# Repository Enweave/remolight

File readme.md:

### ... well, we just mess around with VUE and Wemos

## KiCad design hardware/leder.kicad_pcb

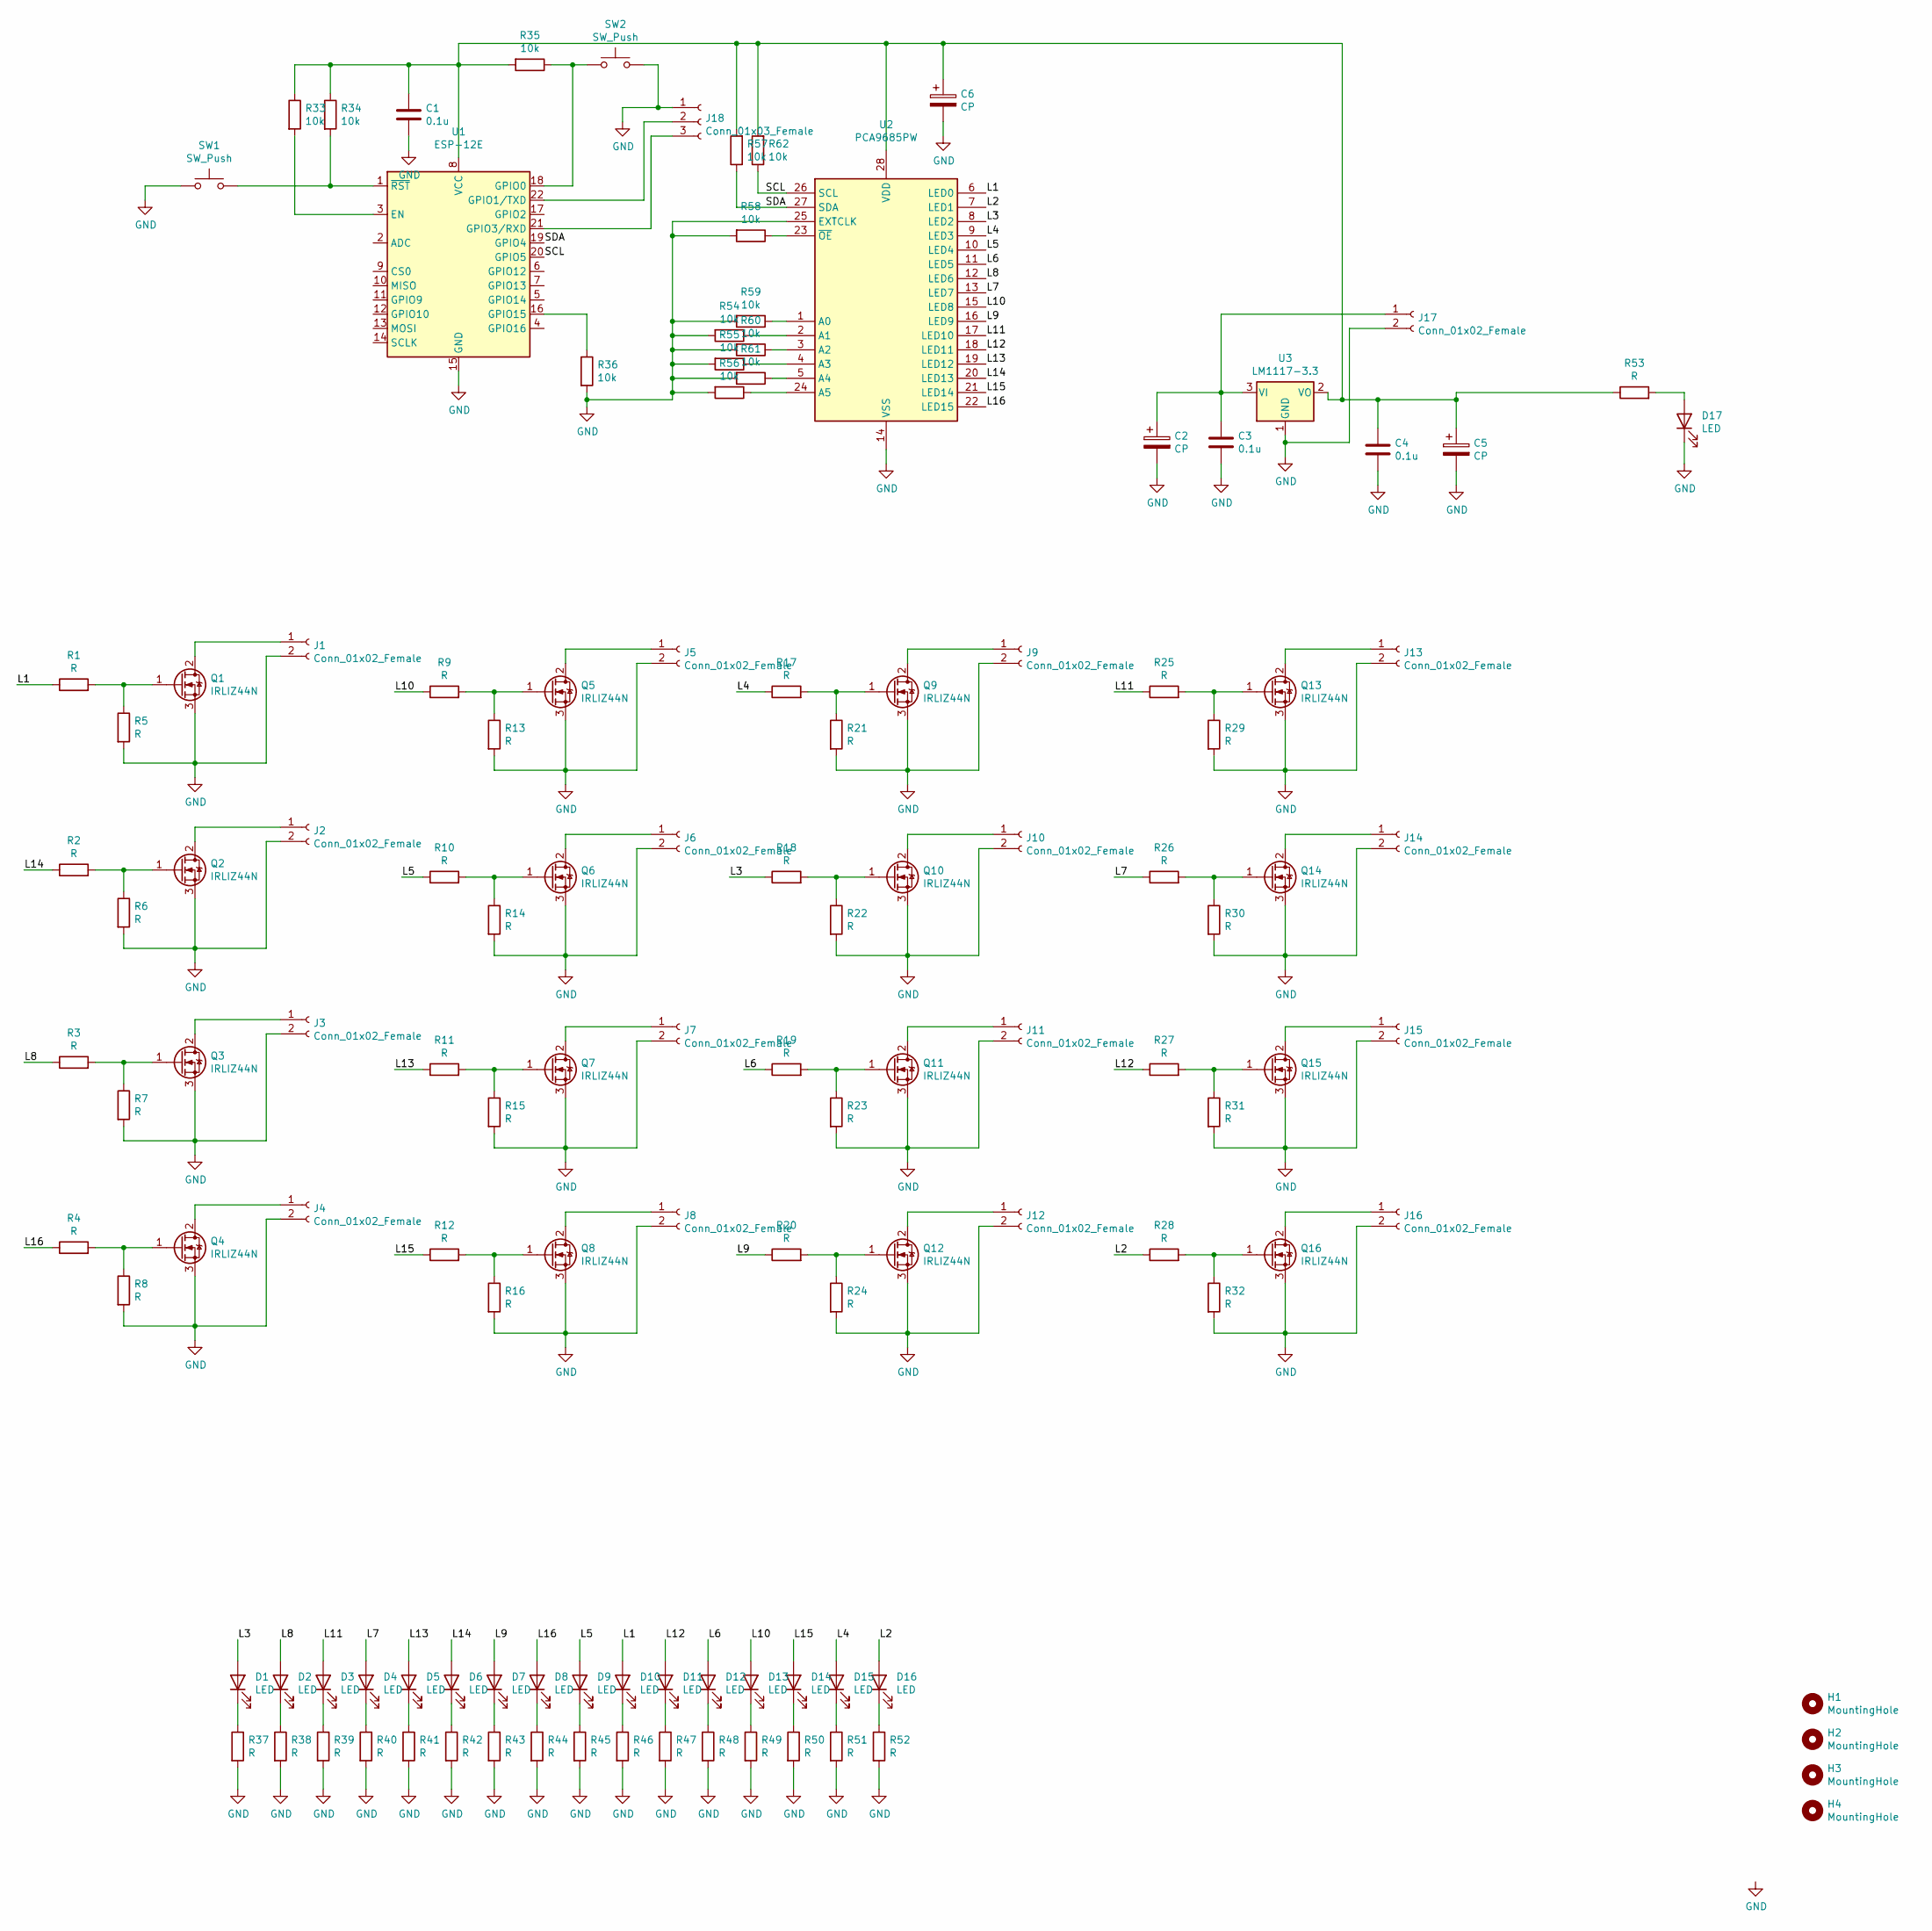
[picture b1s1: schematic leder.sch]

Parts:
C1, C3, C4: 0.1u; C_1206_3216Metric_Pad1.33x1.80mm_HandSolder
C2, C5, C6: CP; CP_Radial_D5.0mm_P2.50mm
D1, D2, D3, D4, D5, D6, D7, D8, D9, D10, D11, D12, D13, D14, D15, D16, D17: LED; LED_D5.0mm
H1, H2, H3, H4: MountingHole; MountingHole_3.2mm_M3_DIN965_Pad
J1, J2, J3, J4, J5, J6, J7, J8, J9, J10, J11, J12, J13, J14, J15, J16, J17: Conn_01x02_Female; PhoenixContact_MSTBA_2,5_2-G_1x02_P5.00mm_Horizontal
J18: Conn_01x03_Female; PinHeader_1x03_P2.54mm_Vertical
Q1, Q2, Q3, Q4, Q5, Q6, Q7, Q8, Q9, Q10, Q11, Q12, Q13, Q14, Q15, Q16: IRLIZ44N; TO-220F-3_Vertical
R1, R2, R3, R4, R5, R6, R7, R8, R9, R10, R11, R12, R13, R14, R15, R16, R17, R18, R19, R20, R21, R22, R23, R24, R25, R26, R27, R28, R29, R30, R31, R32, R37, R38, R39, R40, R41, R42, R43, R44, R45, R46, R47, R48, R49, R50, R51, R52, R53: R; R_1206_3216Metric_Pad1.30x1.75mm_HandSolder
R33, R34, R35, R36, R54, R55, R56, R57, R58, R59, R60, R61, R62: 10k; R_1206_3216Metric_Pad1.30x1.75mm_HandSolder
SW1, SW2: SW_Push; SW_PUSH_6mm_H4.3mm
U1: ESP-12E
U2: PCA9685PW; TSSOP-28_4.4x9.7mm_P0.65mm
U3: LM1117-3.3; SOT-223

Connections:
/L1: D10.2 (A), R1.1, U2.6 (LED0)
/L2: D16.2 (A), R28.1, U2.7 (LED1)
/L3: D1.2 (A), R18.1, U2.8 (LED2)
/L4: D15.2 (A), R17.1, U2.9 (LED3)
/L5: D9.2 (A), R10.1, U2.10 (LED4)
/L6: D12.2 (A), R19.1, U2.11 (LED5)
/L7: D4.2 (A), R26.1, U2.13 (LED7)
/L8: D2.2 (A), R3.1, U2.12 (LED6)
/L9: D7.2 (A), R20.1, U2.16 (LED9)
/L10: D13.2 (A), R9.1, U2.15 (LED8)
/L11: D3.2 (A), R25.1, U2.17 (LED10)
/L12: D11.2 (A), R27.1, U2.18 (LED11)
/L13: D5.2 (A), R11.1, U2.19 (LED12)
/L14: D6.2 (A), R2.1, U2.20 (LED13)
/L15: D14.2 (A), R12.1, U2.21 (LED14)
/L16: D8.2 (A), R4.1, U2.22 (LED15)
/SCL: R62.1, U1.20 (GPIO5), U2.26 (SCL)
/SDA: R57.1, U1.19 (GPIO4), U2.27 (SDA)
GND: C1.2, C2.2, C3.2, C4.2, C5.2, C6.2, D17.1 (K), J1.2, J2.2, J3.2, J4.2, J5.2, J6.2, J7.2, J8.2, J9.2, J10.2, J11.2, J12.2, J13.2, J14.2, J15.2, J16.2, J17.2, J18.1, Q1.3 (S), Q2.3 (S), Q3.3 (S), Q4.3 (S), Q5.3 (S), Q6.3 (S), Q7.3 (S), Q8.3 (S), Q9.3 (S), Q10.3 (S), Q11.3 (S), Q12.3 (S), Q13.3 (S), Q14.3 (S), Q15.3 (S), Q16.3 (S), R5.2, R6.2, R7.2, R8.2, R13.2, R14.2, R15.2, R16.2, R21.2, R22.2, R23.2, R24.2, R29.2, R30.2, R31.2, R32.2, R36.2, R37.2, R38.2, R39.2, R40.2, R41.2, R42.2, R43.2, R44.2, R45.2, R46.2, R47.2, R48.2, R49.2, R50.2, R51.2, R52.2, R54.2, R55.2, R56.2, R58.2, R59.2, R60.2, R61.2, SW1.1, SW2.2, U1.15 (GND), U2.14 (VSS), U2.25 (EXTCLK), U3.1 (GND)
unnamed: C1.1, C4.1, C5.1, C6.1, R33.1, R34.1, R35.2, R53.1, R57.2, R62.2, U1.8 (VCC), U2.28 (VDD), U3.2 (VO)
unnamed: C2.1, C3.1, J17.1, U3.3 (VI)
unnamed: D1.1 (K), R37.1
unnamed: D2.1 (K), R38.1
unnamed: D3.1 (K), R39.1
unnamed: D4.1 (K), R40.1
unnamed: D5.1 (K), R41.1
unnamed: D6.1 (K), R42.1
unnamed: D7.1 (K), R43.1
unnamed: D8.1 (K), R44.1
unnamed: D9.1 (K), R45.1
unnamed: D10.1 (K), R46.1
unnamed: D11.1 (K), R47.1
unnamed: D12.1 (K), R48.1
unnamed: D13.1 (K), R49.1
unnamed: D14.1 (K), R50.1
unnamed: D15.1 (K), R51.1
unnamed: D16.1 (K), R52.1
unnamed: D17.2 (A), R53.2
unnamed: J1.1, Q1.2 (D)
unnamed: J2.1, Q2.2 (D)
unnamed: J3.1, Q3.2 (D)
unnamed: J4.1, Q4.2 (D)
unnamed: J5.1, Q5.2 (D)
unnamed: J6.1, Q6.2 (D)
unnamed: J7.1, Q7.2 (D)
unnamed: J8.1, Q8.2 (D)
unnamed: J9.1, Q9.2 (D)
unnamed: J10.1, Q10.2 (D)
unnamed: J11.1, Q11.2 (D)
unnamed: J12.1, Q12.2 (D)
unnamed: J13.1, Q13.2 (D)
unnamed: J14.1, Q14.2 (D)
unnamed: J15.1, Q15.2 (D)
unnamed: J16.1, Q16.2 (D)
unnamed: J18.2, U1.22 (GPIO1/TXD)
unnamed: J18.3, U1.21 (GPIO3/RXD)
unnamed: Q1.1 (G), R1.2, R5.1
unnamed: Q2.1 (G), R2.2, R6.1
unnamed: Q3.1 (G), R3.2, R7.1
unnamed: Q4.1 (G), R4.2, R8.1
unnamed: Q5.1 (G), R9.2, R13.1
unnamed: Q6.1 (G), R10.2, R14.1
unnamed: Q7.1 (G), R11.2, R15.1
unnamed: Q8.1 (G), R12.2, R16.1
unnamed: Q9.1 (G), R17.2, R21.1
unnamed: Q10.1 (G), R18.2, R22.1
unnamed: Q11.1 (G), R19.2, R23.1
unnamed: Q12.1 (G), R20.2, R24.1
unnamed: Q13.1 (G), R25.2, R29.1
unnamed: Q14.1 (G), R26.2, R30.1
unnamed: Q15.1 (G), R27.2, R31.1
unnamed: Q16.1 (G), R28.2, R32.1
unnamed: R33.2, U1.3 (EN)
unnamed: R34.2, SW1.2, U1.1 (~RST)
unnamed: R35.1, SW2.1, U1.18 (GPIO0)
unnamed: R36.1, U1.16 (GPIO15)
unnamed: R54.1, U2.2 (A1)
unnamed: R55.1, U2.4 (A3)
unnamed: R56.1, U2.24 (A5)
unnamed: R58.1, U2.23 (~OE)
unnamed: R59.1, U2.1 (A0)
unnamed: R60.1, U2.3 (A2)
unnamed: R61.1, U2.5 (A4)

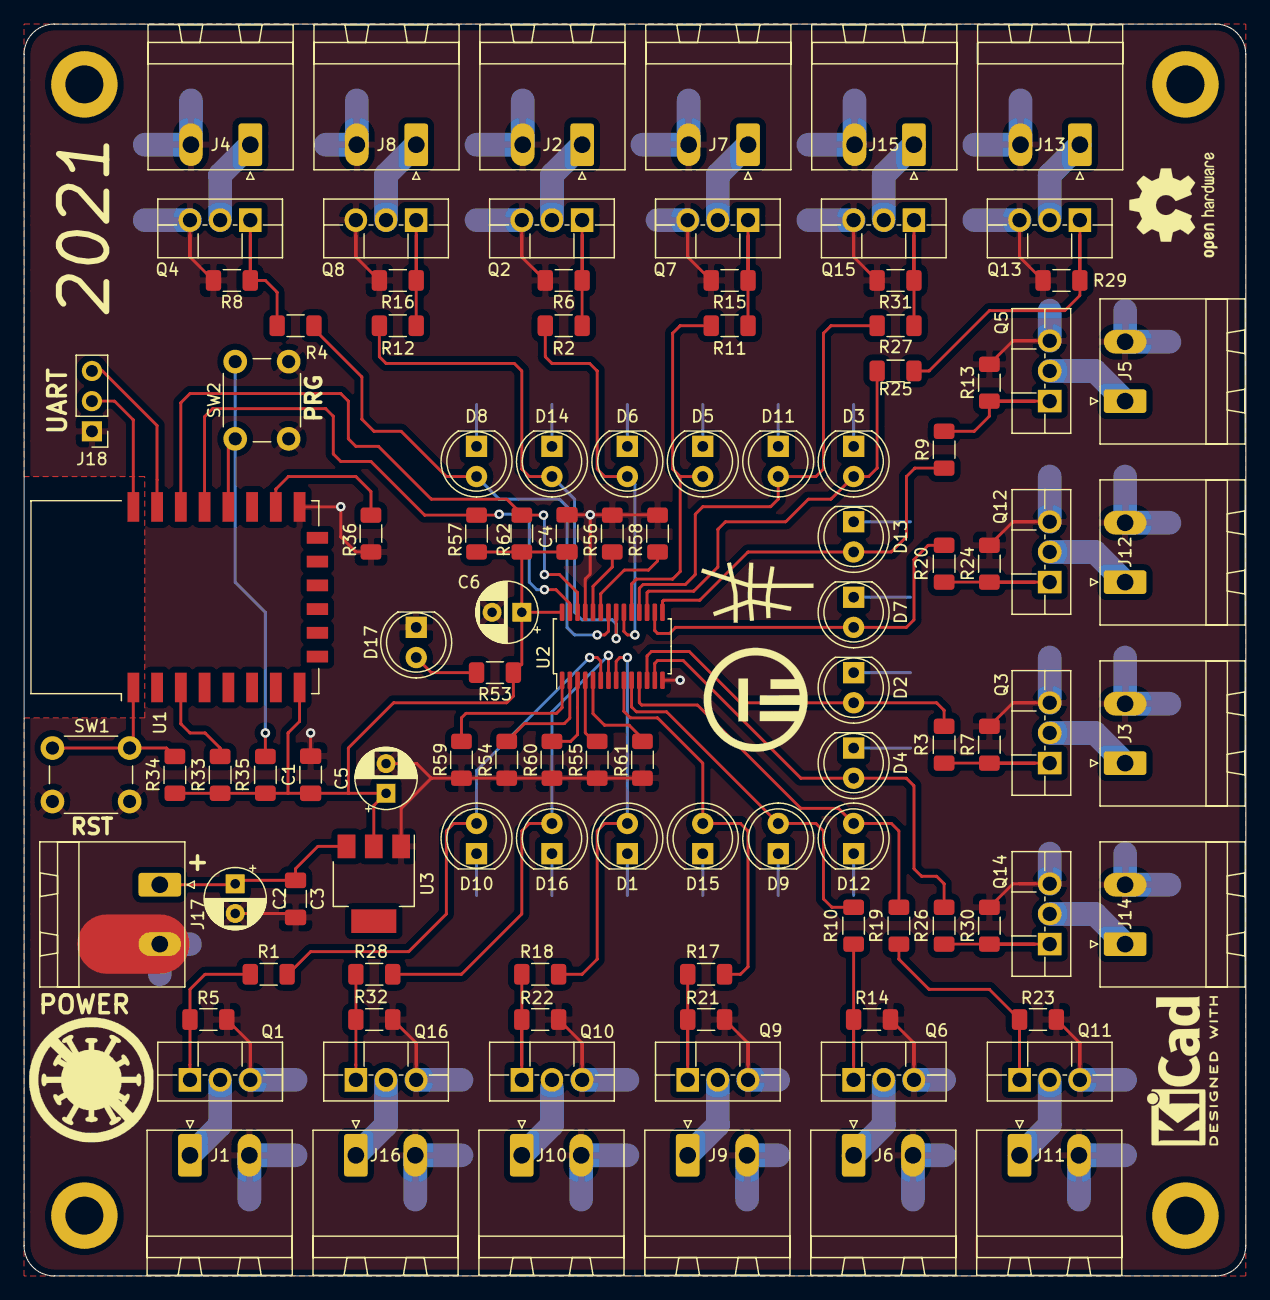
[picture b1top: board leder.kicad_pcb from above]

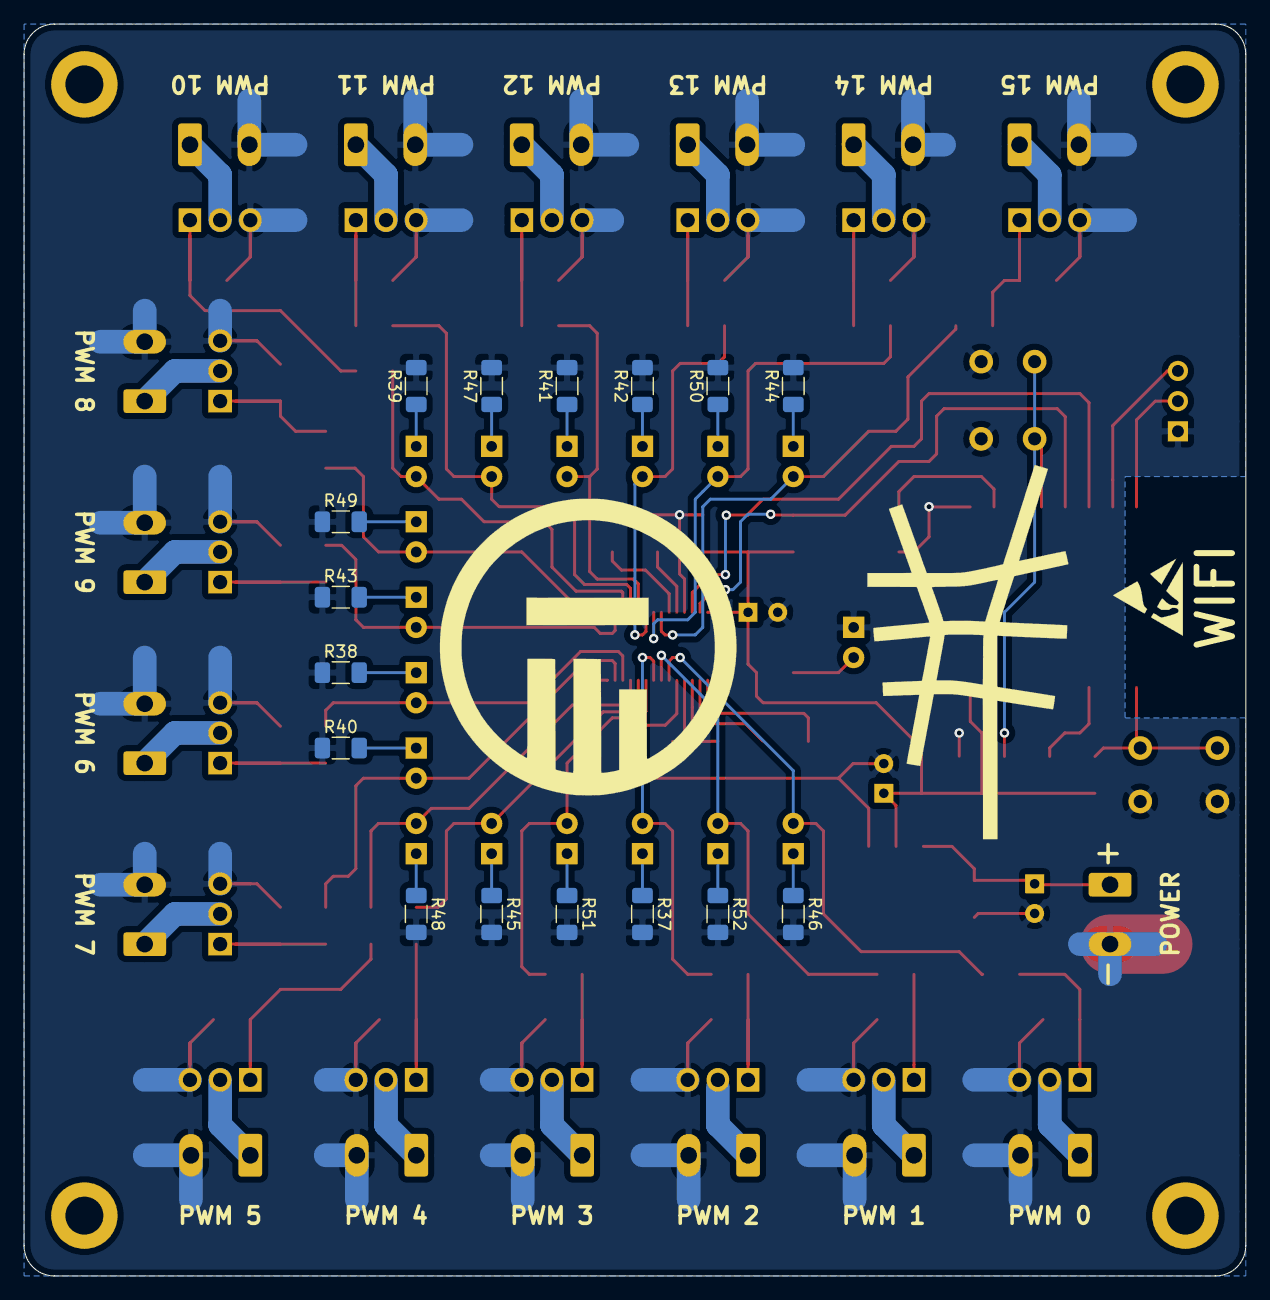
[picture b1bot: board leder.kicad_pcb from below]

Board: 2 copper layers, 102.9 x 105.4 mm, 128 parts (16 on the bottom side), 83 nets.

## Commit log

2021-11-23 init
2021-11-23 add vue config
2021-11-23 Look, mum, I've made hello world!
2021-11-23 index block
2021-11-23 add arduino src
2021-11-24 update arduino
2021-11-24 Update arduino project
2021-11-24 add hardware project
2021-11-24 rename arduino
2021-11-24 new update
2021-11-24 test server + basic form
2021-11-25 fix form data + dark theme
2021-11-26 add icons
2021-11-26 add SW and kinda configure PWA
2021-11-26 add instruction for getting https working on localhost
2021-11-26 workbox + service_worker
2022-01-02 dumb jquery proto
2022-01-19 add helper for start developments
